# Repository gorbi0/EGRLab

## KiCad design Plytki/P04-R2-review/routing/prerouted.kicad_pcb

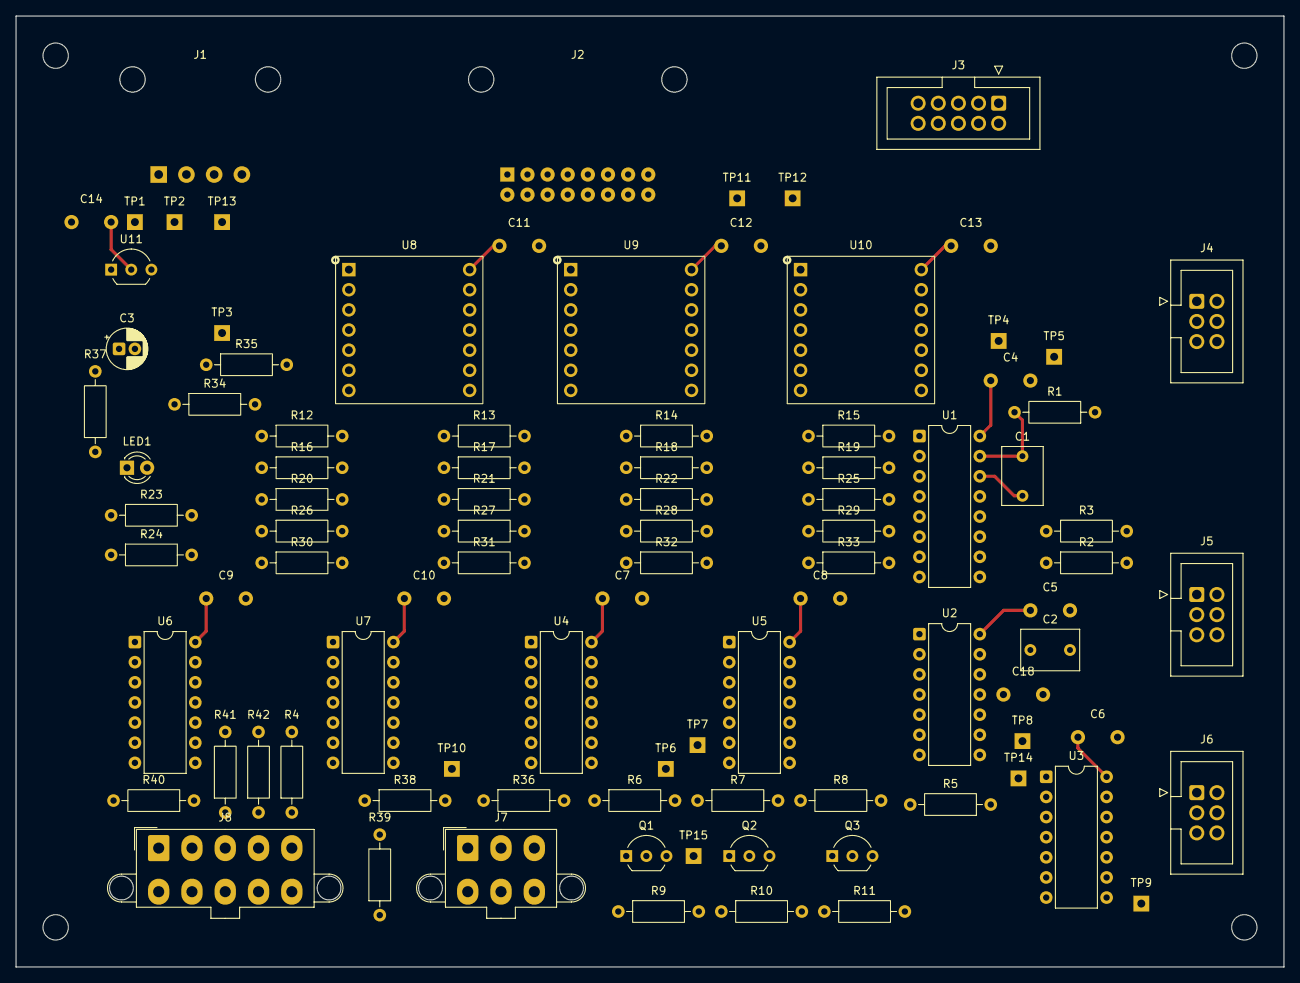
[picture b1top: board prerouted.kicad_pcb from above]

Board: 2 copper layers, 160.0 x 120.0 mm, 99 parts (0 on the bottom side), 67 nets.

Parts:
C1, C2: 1u; C_Rect_L7.2mm_W5.0mm_P5.00mm
C3: 10u; CP_Radial_D5.0mm_P2.00mm
C4, C5, C6, C7, C8, C9, C10, C11, C12, C13, C14: 100n; C_Vishay_K15_H5_P5
C18: 1n; C_Vishay_K15_H5_P5
H1, H2, H3, H4: M3 NPTH
J1: LV04; PTH_LV04_4p_AWG22
J2: SAFE; PTH_SAFE_16p_AWG28
J3: DRIVE; IDC_10p_Wurth_Drill1.2
J4: SENSOR; IDC_6p_Wurth_Drill1.2
J5: DAQOK; IDC_6p_Wurth_Drill1.2
J6: PSUOK; IDC_6p_Wurth_Drill1.2
J7: PG; Molex_Mini-Fit_Jr_5566-06A2_2x03_P4.20mm_Vertical
J8: PANELSAFE; Molex_Mini-Fit_Jr_5566-10A2_2x05_P4.20mm_Vertical
LED1: POWER; LED_D3.0mm
Q1, Q2, Q3: 2N3904; TO-92_Inline_Wide
R1: 220K; R_Axial_DIN0207_L6.3mm_D2.5mm_P10.16mm_Horizontal
R2, R4, R6, R7, R8, R12, R13, R14, R15, R16, R18, R19, R20, R21, R22, R23, R24, R25, R29, R31, R32, R33, R34, R35, R36: 10K; R_Axial_DIN0207_L6.3mm_D2.5mm_P10.16mm_Horizontal
R3, R37, R38, R39, R41, R42: 1K; R_Axial_DIN0207_L6.3mm_D2.5mm_P10.16mm_Horizontal
R5, R9, R10, R11, R17, R28, R30: 100K; R_Axial_DIN0207_L6.3mm_D2.5mm_P10.16mm_Horizontal
R26, R27: 47K; R_Axial_DIN0207_L6.3mm_D2.5mm_P10.16mm_Horizontal
R40: 100R; R_Axial_DIN0207_L6.3mm_D2.5mm_P10.16mm_Horizontal
TP1: 3V3_IO; TestPad_1
TP2: GND; TestPad_1
TP3: LOCAL_SUP_N; TestPad_1
TP4: SUP_OK; TestPad_1
TP5: WD_Q; TestPad_1
TP6: SAFE_N; TestPad_1
TP7: SAFE_OK; TestPad_1
TP8: ARM_CLK; TestPad_1
TP9: HW_ARMED; TestPad_1
TP10: INTERLOCK; TestPad_1
TP11: MOTOR_PERMIT; TestPad_1
TP12: SENSOR_PERMIT; TestPad_1
TP13: 5V_SYS; TestPad_1
TP14: SAFE_WD; TestPad_1
TP15: Q1_B; TestPad_1
U1: CD74HC123E; DIP-16_W7.62mm
U2: SN74HC14N; DIP-14_W7.62mm
U3: SN74HC74N; DIP-14_W7.62mm
U4, U5, U6, U7: SN74HC08N; DIP-14_W7.62mm
U8, U9, U10: 74LVC125AD; Adapter_SO14_DIP14_W15.24_Kamami575068
U11: MCP100-300DI/TO; TO-92_Inline_Wide

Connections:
3V3_IO: C3.1, C4.1, C5.1, C6.1, C7.1, C8.1, C9.1, C10.1, C11.1, C12.1, C13.1, C14.1, J1.3, R1.1, R2.1, R37.1, R38.1, R39.1, R40.1, TP1.1, U1.16, U2.14, U3.2, U3.4, U3.10, U3.14, U4.14, U5.14, U6.14, U7.14, U8.14, U9.14, U10.13, U10.14, U11.2
5V_SYS: J1.1, TP13.1
/CON/PANEL_3V3: J8.1, R40.2
/CON/PG_3V3: J7.1, R39.2
/CON/PG_SEND: J7.4, R38.2
/ILK/MECH_KEY: U7.5, U7.8
/ILK/MECH_OK_P04: R24.1, R42.2, U7.9
/ILK/MODULES_OK: U7.3, U7.4
/ILK/OK_A: U6.3, U6.12
/ILK/OK_AB: U6.11, U7.1
/ILK/OK_B: U6.6, U6.13
/ILK/OK_C: U6.8, U7.2
/LED_PWR: LED1.2, R37.2
/OUT/ARM_BOTH: U4.3, U4.4
/OUT/MOTOR_REQ: U4.6, U5.12
/OUT/SENSOR_INTERLOCK: U5.3, U5.4
/OUT/SENSOR_KEY: U4.11, U5.1
/WD/ARM_BUTTON_N: C2.1, R2.2, R3.1, U2.3
/WD/ILK_BAD: R8.1, U2.8
/WD/Q1_B: Q1.2, R6.2, R9.1, TP15.1
/WD/Q2_B: Q2.2, R7.2, R10.1
/WD/Q3_B: Q3.2, R8.2, R11.1
/WD/SAFE_OK: TP7.1, U2.12, U7.12
/WD/SAFE_OK_N: U2.10, U2.13
/WD/SUP_BAD: R7.1, U2.6
/WD/SUP_OK: TP4.1, U1.3, U2.5, U5.8
/WD/WD_BAD: R6.1, U2.2
/WD/WD_C: C1.2, U1.14
/WD/WD_Q: TP5.1, U1.13, U2.1, U7.13
/WD/WD_RC: C1.1, R1.2, U1.15
ARM_CLK: J3.5, TP8.1, U2.4, U3.3
ARM_CONTACT: J8.9, R3.2
CORE_LINK: J2.13, R16.1, U9.2
CORE_LINK_P04: R29.1, U6.9, U9.3
DAQ_OK: J5.1, R19.1, U9.12
DAQ_OK_P04: R32.1, U6.2, U9.11
DRIVE_OK: J3.7, R20.1, U10.2
DRIVE_OK_P04: R33.1, U6.4, U10.3
GND: C2.2, C3.2, C4.2, C5.2, C6.2, C7.2, C8.2, C9.2, C10.2, C11.2, C12.2, C13.2, C14.2, C18.2, J1.2, J1.4, J2.2, J2.6, J2.8, J2.10, J2.12, J2.14, J2.16, J3.4, J3.6, J3.8, J3.10, J4.4, J5.2, J6.2, J7.3, J7.6, J8.2, J8.10, LED1.1, Q1.1, Q2.1, Q3.1, R5.2, R9.2, R10.2, R11.2, R12.2, R13.2, R14.2, R15.2, R16.2, R17.2, R18.2, R19.2, R20.2, R21.2, R22.2, R23.2, R24.2, R25.2, R26.2, R27.2, R28.2, R29.2, R30.2, R31.2, R32.2, R33.2, R34.2, R35.2, R36.2, TP2.1, U1.1, U1.8, U1.9, U1.10, U1.11, U2.7, U3.7, U3.11, U3.12, U3.13, U4.7, U5.7, U6.7, U7.7, U8.1, U8.4, U8.7, U8.10, U8.13, U9.1, U9.4, U9.7, U9.10, U9.13, U10.1, U10.4, U10.7, U10.10, U10.12, U11.3
HEARTBEAT: J2.3, R13.1, U8.5
HEARTBEAT_P04: R26.1, U1.2, U8.6
HW_ARMED: J2.7, TP9.1, U3.5, U4.1
INTERLOCK: J2.9, R36.1, TP10.1, U2.9, U4.5, U5.2, U7.6
LOCAL_SUP_N: TP3.1, U5.10, U11.1
MCU_ARM: J2.5, R14.1, U8.9
MCU_ARM_P04: R27.1, U4.2, U8.8
MECH_OK: J8.4, R42.1
MOTOR_PERMIT: J3.1, TP11.1, U4.10, U5.11
PG_LINK: J7.5, R22.1, U10.9
PG_LINK_P04: R35.1, U6.10, U10.8
PSU_OK: J6.1, R18.1, U9.9
PSU_OK_P04: R31.1, U6.1, U9.8
PWM: J2.1, R12.1, U8.2
PWM_OUT: J3.3, U4.8
PWM_P04: R25.1, U4.9, U8.3
SAFE_N: C18.1, J3.9, J7.2, Q1.3, Q2.3, Q3.3, R4.2, R5.1, TP6.1, U2.11
SAFE_WD: TP14.1, U3.1, U5.5, U5.13, U7.11
SENSOR_ENABLE: J2.11, R15.1, U8.12
SENSOR_ENABLE_P04: R28.1, U4.12, U8.11
SENSOR_OK: J4.3, R21.1, U10.5
SENSOR_OK_P04: R34.1, U6.5, U10.6
SENSOR_PERMIT: J4.1, TP12.1, U5.6
STOP_NC_OUT: J8.7, R4.1
SUP_N: J2.15, R17.1, U9.5
SUP_N_P04: R30.1, U5.9, U9.6
TEST_KEY: J8.3, R41.1
TEST_KEY_P04: R23.1, R41.2, U4.13, U7.10
